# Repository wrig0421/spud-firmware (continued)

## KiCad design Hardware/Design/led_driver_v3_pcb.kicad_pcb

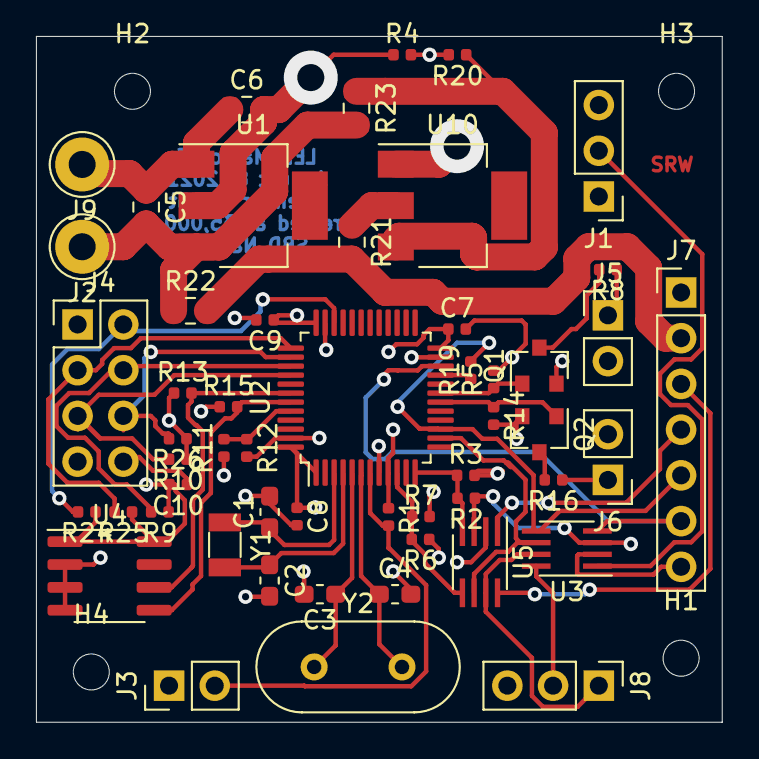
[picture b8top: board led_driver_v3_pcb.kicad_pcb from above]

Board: 4 copper layers, 38.1 x 38.1 mm, 57 parts (0 on the bottom side), 35 nets.

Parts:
C1, C2, C3, C4: CP1_Small; C_0603_1608Metric_Pad1.05x0.95mm_HandSolder
C5, C6: 10u; C_0805_2012Metric
C7, C8, C9, C10: 1u; C_0402_1005Metric
H1, H2, H3, H4: MountingHole_Pad; MountingHole_2mm
J1, J8: Conn_01x03_Male; PinHeader_1x03_P2.54mm_Vertical
J2, J9: Conn_01x01_Male; Pin_D1.3mm_L11.0mm_LooseFit
J3, J5, J6: Conn_01x02_Male; PinHeader_1x02_P2.54mm_Vertical
J4: Conn_01x08_Male; PinHeader_2x04_P2.54mm_Vertical
J7: Conn_01x07_Male; PinHeader_1x07_P2.54mm_Vertical
Q1, Q2: BSS138; SOT-23
R1, R2, R6, R9, R10, R12, R13, R15, R24, R25, R26: 10k; R_0402_1005Metric
R3, R7, R11, R19: DNI; R_0402_1005Metric
R4, R5, R14, R20: 1M; R_0402_1005Metric
R8, R16: 100; R_0402_1005Metric
R21, R22: 0; R_0805_2012Metric
R23: DNI; R_0805_2012Metric
U1, U10: TLV1117-33; SOT-223
U2: STM32L433CCTx; LQFP-48_7x7mm_P0.5mm
U3, U5: TXS0102DCT; SSOP-8_2.95x2.8mm_P0.65mm
U4: CAT24C256; SOIC-8_3.9x4.9mm_P1.27mm
Y1: 32.768k Crystal; Crystal_SMD_3215-2Pin_3.2x1.5mm
Y2: 8M; Crystal_HC49-U_Vertical

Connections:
+3V3: C6.2, C7.1, C8.1, C9.1, C10.2, J4.1, R1.1, R2.1, R4.1, R6.1, R9.1, R10.1, R11.1, R13.1, R15.1, R24.1, R25.1, R26.1, U1.2, U2.1, U2.9, U2.24, U2.36, U2.48, U3.3, U4.1, U4.8, U5.3
/12V_EN: R20.1, R23.1, U10.3
/GRN_LED: Q1.1, R5.1, U2.19
/I2C1_SCL: R13.2, U2.42, U4.6
/I2C1_SDA: R15.2, U2.43, U4.5
/INT2: R6.2, R7.1, U2.10, U5.5
/INT2_5V: J7.3, U5.8
/INT3: R2.2, R3.1, U2.12, U5.4
/INT3_5V: J7.4, U5.1
/LED_STRIP_OUT_1: J8.2, U3.8
/LED_STRIP_OUT_2: J1.2, U3.1
/LVL_SHIFTER_EN: U2.14, U3.6, U5.6
/NJTRST: J4.5, R10.2, U2.40
/RED_LED: Q2.1, R14.1, U2.18
/RST: J3.2, R1.2, U2.7
/STM32_LED_STRIP_OUT_1: J7.5, R19.2, U2.15, U3.5
/STM32_LED_STRIP_OUT_2: J7.6, U2.22, U3.4
/STM32_LED_STRIP_OUT_BACKUP: R19.1, U2.21
/SWCLK: J4.3, R25.2, U2.37
/SWDIO: J4.2, R24.2, U2.34
/SWO: J4.4, R9.2, U2.39
/SYS_5V: J1.1, J5.2, J6.2, J7.2, J8.1, R21.2, R22.2, U3.7, U5.7
/TDI: J4.6, R26.2, U2.38
/VIN: C5.2, J2.1, R22.1, R23.2, U1.3
/XTAL1: C1.1, U2.3, Y1.2
/XTAL1_HI: C3.1, U2.5, Y2.1
/XTAL2: C2.1, U2.4, Y1.1
/XTAL2_HI: C4.1, U2.6, Y2.2
GND: C1.2, C2.2, C3.2, C4.2, C5.1, C6.1, C7.2, C8.2, C9.2, C10.1, J1.3, J3.1, J4.8, J7.1, J7.7, J8.3, J9.1, Q1.2, Q2.2, R3.2, R4.2, R5.2, R7.2, R12.2, R14.2, R20.2, U1.1, U2.8, U2.23, U2.35, U2.47, U3.2, U4.2, U4.3, U4.4, U5.2, U10.1
unnamed: J5.1, R8.1
unnamed: J6.1, R16.1
unnamed: Q1.3, R8.2
unnamed: Q2.3, R16.2
unnamed: R11.2, R12.1, U2.44
unnamed: R21.1, U10.2

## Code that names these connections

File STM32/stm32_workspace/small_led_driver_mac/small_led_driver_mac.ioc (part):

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Mcu.Name=STM32L431R(B-C)Tx
Mcu.Package=LQFP64
Mcu.UserName=STM32L431RCTx
PA0.GPIOParameters=GPIO_ModeDefaultEXTI
PA0.GPIO_ModeDefaultEXTI=GPIO_MODE_IT_FALLING
PA0.Signal=GPXTI0
PA10.Signal=S_TIM1_CH3
PA13\ (JTMS-SWDIO).Mode=JTAG_5_pins
PA13\ (JTMS-SWDIO).Signal=SYS_JTMS-SWDIO
PA14\ (JTCK-SWCLK).Mode=JTAG_5_pins
PA14\ (JTCK-SWCLK).Signal=SYS_JTCK-SWCLK
PA15\ (JTDI).Mode=JTAG_5_pins
PA15\ (JTDI).Signal=SYS_JTDI
PA2.GPIOParameters=GPIO_ModeDefaultEXTI
PA2.GPIO_ModeDefaultEXTI=GPIO_MODE_IT_FALLING
PA2.Signal=GPXTI2
PA6.GPIOParameters=GPIO_Label
PA6.GPIO_Label=TIM16_CH1
PA6.Signal=S_TIM16_CH1
PA8.GPIOParameters=GPIO_Label
PA8.GPIO_Label=TIM1_CH1
PA8.Signal=S_TIM1_CH1
PA9.Signal=S_TIM1_CH2
PB0.GPIOParameters=GPIO_Label
PB0.GPIO_Label=LVL_SHIFTER_EN
PB0.Signal=GPIO_Output
PB14.Signal=S_TIM15_CH1
PB3\ (JTDO-TRACESWO).Mode=JTAG_5_pins
PB3\ (JTDO-TRACESWO).Signal=SYS_JTDO-SWO
PB4\ (NJTRST).Mode=JTAG_5_pins
PB4\ (NJTRST).Signal=SYS_JTRST
PB8.GPIOParameters=GPIO_Label
PB8.GPIO_Label=GPIO_0
PB8.Signal=GPIO_Output
PC0.GPIOParameters=GPIO_Label
PC0.GPIO_Label=GPIO_2
PC0.Signal=GPIO_Output
PC1.GPIOParameters=GPIO_Label
PC1.GPIO_Label=GPIO_3
PC1.Signal=GPIO_Output
PC13.GPIOParameters=GPIO_ModeDefaultEXTI
PC13.GPIO_ModeDefaultEXTI=GPIO_MODE_IT_FALLING
PC13.Signal=GPXTI13
PC14-OSC32_IN\ (PC14).Mode=LSE-External-Oscillator
PC14-OSC32_IN\ (PC14).Signal=RCC_OSC32_IN
PC15-OSC32_OUT\ (PC15).Mode=LSE-External-Oscillator
PC15-OSC32_OUT\ (PC15).Signal=RCC_OSC32_OUT
PC2.GPIOParameters=GPIO_Label
PC2.GPIO_Label=LED_OUT_1
PC2.Signal=GPIO_Output
PC3.GPIOParameters=GPIO_Label
PC3.GPIO_Label=LED_OUT_2
PC3.Signal=GPIO_Output
PC5.GPIOParameters=GPIO_ModeDefaultEXTI
PC5.GPIO_ModeDefaultEXTI=GPIO_MODE_IT_FALLING
PC5.Signal=GPXTI5
PH0-OSC_IN\ (PH0).Mode=HSE-External-Oscillator
PH0-OSC_IN\ (PH0).Signal=RCC_OSC_IN
PH1-OSC_OUT\ (PH1).Mode=HSE-External-Oscillator
PH1-OSC_OUT\ (PH1).Signal=RCC_OSC_OUT
RCC.HSE_VALUE=48000000
RCC.SYSCLKFreq_VALUE=48000000
RCC.SYSCLKSource=RCC_SYSCLKSOURCE_HSE
board=custom

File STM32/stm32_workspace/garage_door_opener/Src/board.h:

/*
 * board.h
 *
 *  Created on: Mar 31, 2021
 *      Author: spud
 */

#ifndef SRC_BOARD_H_
#define SRC_BOARD_H_

#include "stm32l4xx_hal.h"

#define PORTA		GPIOA
#define PIOA_PIN0	GPIO_PIN_0
#define PIOA_PIN1	GPIO_PIN_1
#define PIOA_PIN2	GPIO_PIN_2
#define PIOA_PIN3	GPIO_PIN_3
#define PIOA_PIN4	GPIO_PIN_4
#define PIOA_PIN5	GPIO_PIN_5
#define PIOA_PIN6	GPIO_PIN_6
#define PIOA_PIN7	GPIO_PIN_7
#define PIOA_PIN8	GPIO_PIN_8
#define PIOA_PIN9	GPIO_PIN_9
#define PIOA_PIN10	GPIO_PIN_10
#define PIOA_PIN11	GPIO_PIN_11
#define PIOA_PIN12	GPIO_PIN_12
#define PIOA_PIN13	GPIO_PIN_13
#define PIOA_PIN14	GPIO_PIN_14
#define PIOA_PIN15	GPIO_PIN_15

#define PORTB		GPIOB
#define PIOB_PIN0	GPIO_PIN_0
#define PIOB_PIN1	GPIO_PIN_1
#define PIOB_PIN2	GPIO_PIN_2
#define PIOB_PIN3	GPIO_PIN_3
#define PIOB_PIN4	GPIO_PIN_4
#define PIOB_PIN5	GPIO_PIN_5
#define PIOB_PIN6	GPIO_PIN_6
#define PIOB_PIN7	GPIO_PIN_7
#define PIOB_PIN8	GPIO_PIN_8
#define PIOB_PIN9	GPIO_PIN_9
#define PIOB_PIN10	GPIO_PIN_10
#define PIOB_PIN11	GPIO_PIN_11
#define PIOB_PIN12	GPIO_PIN_12
#define PIOB_PIN13	GPIO_PIN_13
#define PIOB_PIN14	GPIO_PIN_14
#define PIOB_PIN15	GPIO_PIN_15

#define PORTC		GPIOC
#define PIOC_PIN13	GPIO_PIN_13
#define PIOC_PIN14	GPIO_PIN_14
#define PIOC_PIN15	GPIO_PIN_15

#define PORTH		GPIOH
#define PIOH_PIN0	GPIO_PIN_0
#define PIOH_PIN1	GPIO_PIN_1
#define PIOH_PIN3	GPIO_PIN_3

// PORTA
#define INT2						PIOA_PIN0
#define INT3						PIOA_PIN2
#define LVL_SHIFTER_EN				PIOA_PIN4
#define STM32_LED_STRIP_OUT			PIOA_PIN5
#define SWDIO						PIOA_PIN13
#define SWCLK						PIOA_PIN14
#define TDI							PIOA_PIN15

// PORTB
#define RED_LED						PIOB_PIN0
#define GRN_LED						PIOB_PIN1
#define SWO							PIOB_PIN3
#define NJTRST						PIOB_PIN4
#define I2C1_SCL					PIOB_PIN6
#define I2C1_SDA					PIOB_PIN7
#define STM32_LED_STRIP_OUT_BACKUP	PIOB_PIN10

// PORTC
#define INT1						PIOC_PIN13

#define	IOPORT_PIN_LEVEL_LOW		GPIO_PIN_RESET
#define	IOPORT_PIN_LEVEL_HIGH		GPIO_PIN_SET


#endif /* SRC_BOARD_H_ */

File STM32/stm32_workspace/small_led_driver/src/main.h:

/* USER CODE BEGIN Header */
/**
  ******************************************************************************
  * @file           : main.h
  * @brief          : Header for main.c file.
  *                   This file contains the common defines of the application.
  ******************************************************************************
  * @attention
  *
  * <h2><center>&copy; Copyright (c) 2022 STMicroelectronics.
  * All rights reserved.</center></h2>
  *
  * This software component is licensed by ST under BSD 3-Clause license,
  * the "License"; You may not use this file except in compliance with the
  * License. You may obtain a copy of the License at:
  *                        opensource.org/licenses/BSD-3-Clause
  *
  ******************************************************************************
  */
/* USER CODE END Header */

/* Define to prevent recursive inclusion -------------------------------------*/
#ifndef __MAIN_H
#define __MAIN_H

#ifdef __cplusplus
extern "C" {
#endif

/* Includes ------------------------------------------------------------------*/
#include "stm32l4xx_hal.h"

/* Private includes ----------------------------------------------------------*/
/* USER CODE BEGIN Includes */

/* USER CODE END Includes */

/* Exported types ------------------------------------------------------------*/
/* USER CODE BEGIN ET */

/* USER CODE END ET */

/* Exported constants --------------------------------------------------------*/
/* USER CODE BEGIN EC */

/* USER CODE END EC */

/* Exported macro ------------------------------------------------------------*/
/* USER CODE BEGIN EM */

/* USER CODE END EM */

void HAL_TIM_MspPostInit(TIM_HandleTypeDef *htim);

/* Exported functions prototypes ---------------------------------------------*/
void Error_Handler(void);

/* USER CODE BEGIN EFP */

/* USER CODE END EFP */

/* Private defines -----------------------------------------------------------*/
#define WKUP2_Pin GPIO_PIN_13
#define WKUP2_GPIO_Port GPIOC
#define GPIO_2_Pin GPIO_PIN_0
#define GPIO_2_GPIO_Port GPIOC
#define GPIO_3_Pin GPIO_PIN_1
#define GPIO_3_GPIO_Port GPIOC
#define LED_OUT_1_Pin GPIO_PIN_2
#define LED_OUT_1_GPIO_Port GPIOC
#define LED_OUT_2_Pin GPIO_PIN_3
#define LED_OUT_2_GPIO_Port GPIOC
#define WKUP1_Pin GPIO_PIN_0
#define WKUP1_GPIO_Port GPIOA
#define TIM2_CH2_Pin GPIO_PIN_1
#define TIM2_CH2_GPIO_Port GPIOA
#define WKUP4_Pin GPIO_PIN_2
#define WKUP4_GPIO_Port GPIOA
#define TIM15_CH1_Pin GPIO_PIN_3
#define TIM15_CH1_GPIO_Port GPIOA
#define TIM16_CH1_Pin GPIO_PIN_6
#define TIM16_CH1_GPIO_Port GPIOA
#define WKUP3_Pin GPIO_PIN_5
#define WKUP3_GPIO_Port GPIOC
#define LEVEL_SHIFTER_EN_Pin GPIO_PIN_0
#define LEVEL_SHIFTER_EN_GPIO_Port GPIOB
#define TIM1_CH1_Pin GPIO_PIN_8
#define TIM1_CH1_GPIO_Port GPIOA
#define GPIO_0_Pin GPIO_PIN_8
#define GPIO_0_GPIO_Port GPIOB
/* USER CODE BEGIN Private defines */

/* USER CODE END Private defines */

#ifdef __cplusplus
}
#endif

#endif /* __MAIN_H */

/************************ (C) COPYRIGHT STMicroelectronics *****END OF FILE****/

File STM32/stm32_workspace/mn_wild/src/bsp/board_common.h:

// SRW

#if !defined(BOARD_COMMON_H)
#define BOARD_COMMON_H


// PORTA pins
#define PIN_PORT_A                  GPIOA

#define PIN_WKUP_1                  GPIO_PIN_0
#define PIN_ADAFRUIT_RESET_N        GPIO_PIN_1
#define PIN_WKUP_4                  GPIO_PIN_2
#define PIN_ADAFRUIT_TRIG_0         GPIO_PIN_3
#define PIN_ADAFRUIT_TRIG_1         GPIO_PIN_4
#define PIN_ADAFRUIT_TRIG_2         GPIO_PIN_5
#define PIN_ADAFRUIT_TRIG_3         GPIO_PIN_6
#define PIN_ADAFRUIT_TRIG_4         GPIO_PIN_7
#define PIN_TIM1_CH1                GPIO_PIN_8
#define PIN_LVL_DIR                 GPIO_PIN_9
#define PIN_LVL_EN                  GPIO_PIN_10
#define PIN_LIGHT_CTRL              GPIO_PIN_11
#define PIN_SPEAKER_CTRL            GPIO_PIN_12


// PORTB pins
#define PIN_PORT_B                  GPIOB

#define PIN_GPIO_0                  GPIO_PIN_0
#define PIN_GPIO_1                  GPIO_PIN_1
#define PIN_GPIO_2                  GPIO_PIN_2

#define PIN_GPIO_7                  GPIO_PIN_5
#define PIN_GPIO_6                  GPIO_PIN_6
#define PIN_GPIO_5                  GPIO_PIN_7
#define PIN_GPIO_4                  GPIO_PIN_8

#define PIN_I2C2_SCL                GPIO_PIN_10
#define PIN_I2C2_SDA                GPIO_PIN_11
#define PIN_ADAFRUIT_TRIG_6         GPIO_PIN_12
#define PIN_ADAFRUIT_TRIG_7         GPIO_PIN_13
#define PIN_ADAFRUIT_TRIG_8         GPIO_PIN_14
#define PIN_ADAFRUIT_TRIG_9         GPIO_PIN_15


// PORTC pins
#define PIN_PORT_C                  GPIOC

#define PIN_LPUART1_RX              GPIO_PIN_0
#define PIN_LPUART1_TX              GPIO_PIN_1
#define PIN_LED_OUT_1               GPIO_PIN_2
#define RED_LED                     PIN_LED_OUT_1
#define PIN_LED_OUT_2               GPIO_PIN_3
#define GREEN_LED                   PIN_LED_OUT_2

#define PIN_ADAFRUIT_TRIG_5         GPIO_PIN_4
#define PIN_WKUP_3                  GPIO_PIN_5
#define PIN_ADAFRUIT_TRIG_10        GPIO_PIN_6
#define PIN_ADAFRUIT_ACT            GPIO_PIN_7
#define PIN_ADAFRUIT_PWR_EN         GPIO_PIN_8
#define PIN_GPIO_3                  GPIO_PIN_9
#define PIN_ADAFRUIT_VOL_DOWN       GPIO_PIN_10
#define PIN_ADAFRUIT_VOL_UP         GPIO_PIN_11
#define PIN_ADAFRUIT_UART_ENABLE_N  GPIO_PIN_12
#define PIN_WKUP_2                  GPIO_PIN_13
#define PIN_OSC32_HI                GPIO_PIN_14
#define PIN_OSC32_LO                GPIO_PIN_15



#endif

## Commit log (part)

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2020-03-28 together sign initial upload
2020-05-08 nohbz sign code upload.. known issue with interrupts in adafruit library. Debugging currently
2020-05-09 nohbz_sign_release_code
2020-05-10 final release code
2020-06-20 spud sign initial support
2020-09-12 red_bull sign simple code
2021-02-01 retry..
2021-02-01 add mint state for little noble
2021-04-03 stm32 led driver code
2021-05-22 schumacher_sign
2021-05-27 wedding changes
2021-06-05 Schumacher wedding 2021 release
    This code was used on both "Together" & "Schunacher" signs. Congrats to Sarah & Alec.
2021-06-18 finger_print code
2021-06-19 fingerprint driver mods
2021-06-19 wkup src working, rtos & gt521fx working
2021-06-22 keypad working
2021-06-23 open door is short circuiting currently. Needs further debugging
2021-06-27 pkt queue fixes. Need to figure out pkt receive issues. False positives occurring
2021-07-02 code cleanup
2021-07-25 changes towards final ssd1351 fingerprint sensor
2021-09-01 latest & greatest for Spuds sign
2021-11-20 create mn_wild_project
2021-11-22 mn wild project test code updload
2022-01-04 animate_led + color_led lib updates
    Add support for up to 9 strips. Good Vibes sign is the first sign that uses more than one strip.
2022-01-05 simplified animate_led library. Added additional animation support
    Created a new "sparkle" animation from a bug finding. Choosing to not fill the "sparkle" LED w/ black after turning on. This causes sparkle LED to overlay on previous animation which looks very cool.
2022-01-31 good vibes updates 1/30
2022-02-11 add support for multiple colors in a single animation
2022-02-14 add changes to allow external interrupts to be re-enabled. Needs to be tested on HW.
2022-02-20 remove the redundant division by brigthness divisor
2022-05-12 add hardware repo
2022-06-18 reorganize stm32 code 001
2022-06-19 stm32 reorganization led lib updates
2022-06-19 more updates...
2022-06-19 latest
2022-06-19 more changes..
2022-06-20 freertos added
2022-07-02 pattys pub last minute push
2022-07-02 #latest #greatest only the best for Mr. Keefe
2022-07-04 djdj
2022-07-09 srw_updating
2022-07-30 update based on testing of new level shifter
2022-07-31 mac project added
2022-07-31 latest & greatest
2022-08-06 mac commit
2022-08-06 add board_specific files for the different hardware
2022-08-06 need to add these files to git ignore!!!
2022-09-05 reorganize stuff
2022-09-25 windows project commit!
2022-09-25 changes to get the windows version of spuglo working!
2022-10-11 add task_button_press changes
2022-11-05 refactor some red, green, blue variable defs...
2022-12-04 plane updates
2023-01-15 Code sync for kruse sign
2023-01-15 remove duplicate hardware
2023-02-25 start adding flash parameters
2023-03-12 separate tasks for each LED strip
2023-03-28 uart setup
2023-04-29 latest code with UART working on spudglo_v4p2
2023-04-29 spudglo building (no errors) on imac
2023-04-30 uart working... Only when using windows with EXAR app
2023-04-30 spudglov4p2_leds_working!
2023-04-30 #latest #greatest
2023-05-11 lpuart testing
2023-05-12 changes to reorg bsp
2023-05-24 button interrupts working on spudglo v4p2
2023-05-25 final code flashed to spudglo RESS sign
2023-08-05 code updating flash info values
2023-08-06 more flash changes
2023-08-06 flash writes working!
2023-08-13 flash reads/writes working
    flash reads/writes working
2023-08-22 save changes before branch switch..
2023-09-04 rand_color + rand_animation add
2023-09-04 starting to add in the flash info hooks to task_led
2023-11-03 gpio_config start
2023-11-22 add spudglo v4p3 to the stable fw branch
2023-12-15 minor tweaks to stable code
2023-12-15 minor tweaks
2023-12-15 add counts for button presses
2023-12-15 adding peripheral layers..
2023-12-19 uart, spi layers WIP
2023-12-19 spi, uart layers are compiling
2023-12-25 FINAL CODE FLASHED TO SCHUMACHER SIGN
2023-12-27 AT COMMANDS WORKING WITH ESP8266
2023-12-27 push to transfer to imac
2023-12-28 webserver working
2023-12-29 firmware coming down from webserver. Need to properly parse the +IPD pieces. This is corrupting flash.. They are inserted to chunk data coming from server. Tomorrow...
2024-01-23 latest...
2024-01-23 full send on the WS2812B driver. Forgot how cluttered this was
2024-01-25 remove strip_bit only use strip_num
2024-01-26 That sucked. Remove Alec's mallord default setting....f*** me
2024-01-27 cleaning up led driver lib
2024-01-27 fix build errors!!
2024-02-02 commit prior to revert for snowflake...
2024-02-03 multiple strips working again. Error in DMA clock enable call. Needs to be called before used...
2024-02-03 multiple strips verified working on SpudGlo v6 board!!
2024-02-04 straightening out task_led_ctrl. Global struct used for tracking now..
2024-02-11 latest, greatest changes
2024-02-13 vice_city_final_code
2024-03-08 code flashed before delivering
2024-03-31 checkpoint... i2c setup for SpudGlo v7 happening..
2024-04-05 really tearing stuff up here. A lot of architecture changes that will drive improved handling of multiple strip signs.
2024-04-05 another checkpoint... working through build errors.
2024-04-05 another checkpoint.. Probably 75% through the build errors.
2024-04-05 100% compiling.. A few warnings to go through now. Major changes to the handling of strips. All functions will take the strip mask as an argument.
2024-04-05 warnings suppressed..
2024-04-09 another check point!!
2024-04-25 straigten out the DMA buffers. Individual buffers for each LED strip
2024-05-22 adding iteration max for each LED speed
2024-05-25 FIXED FLICKER ISSUE. RESET CYCLE time was incorrect... Also added 1 ms delay after DMA cmplt.. This was the main cause of clicker issue..
2024-05-27 3rd led driver working
2024-05-31 jhkgjkg
2024-06-01 rv8803 I2c writes/reads working
2024-06-08 re-enable standard task sync operation
2024-06-08 freertos files updated to 202212.01
2024-07-16 refactored task_button_press
2024-07-19 task_button_press working following refactor
2024-07-21 move code to new files..
2024-07-21 working through testing each led state
2024-07-23 trying to get code to run without debugger attached
2024-08-03 final code loaded to brady keefe's sign... An incredible final push
2024-08-13 zabinski sign
2024-08-18 final code loaded to zabinski sign
2024-09-14 fall sign
2024-09-21 punkin thupport
2024-09-21 quick + dirty timer addition.
2024-09-23 start updating spudglo pcb board
2024-10-13 checkpoint prior to adding clock support code
2024-10-13 refactor rv8803 slightly
2024-12-27 latest harley morninville sign!
2024-12-27 before tearing out init function
2024-12-27 morinville_sign checkpoint
2024-12-27 final_code_loaded_to_mornville_sign
2025-03-02 kjgkg
2025-06-02 stable-working-spudglo-code
2025-06-20 uart code working!
2025-06-25 uart dma working
2025-11-29 TX ONLY working... RX not working for some reason...potentially the board?
2026-02-06 work through cleaning up led_animate file.. Add function headers and be more consistent with strip_mask_t usage!
2026-02-06 working through ws2812 changes. mostly function comment headers
2026-02-14 dual LED strips "working"
2026-03-04 access layer for led_ctrl...
2026-03-05 working through build errors
2026-03-05 build errors resolved
2026-03-06 task_button_press led flashes WORKING. TASK NOTIFICATION MESSED UP THE FLASH
2026-03-06 timing working again for each animation... state change kills led ctrl 1 it appears
2026-03-06 FINAL CORMICAN SIGN CODE...
2026-04-05 savepoint
2026-04-12 starting to add support for spudglo 8, 9
2026-05-16 commit latest changes
